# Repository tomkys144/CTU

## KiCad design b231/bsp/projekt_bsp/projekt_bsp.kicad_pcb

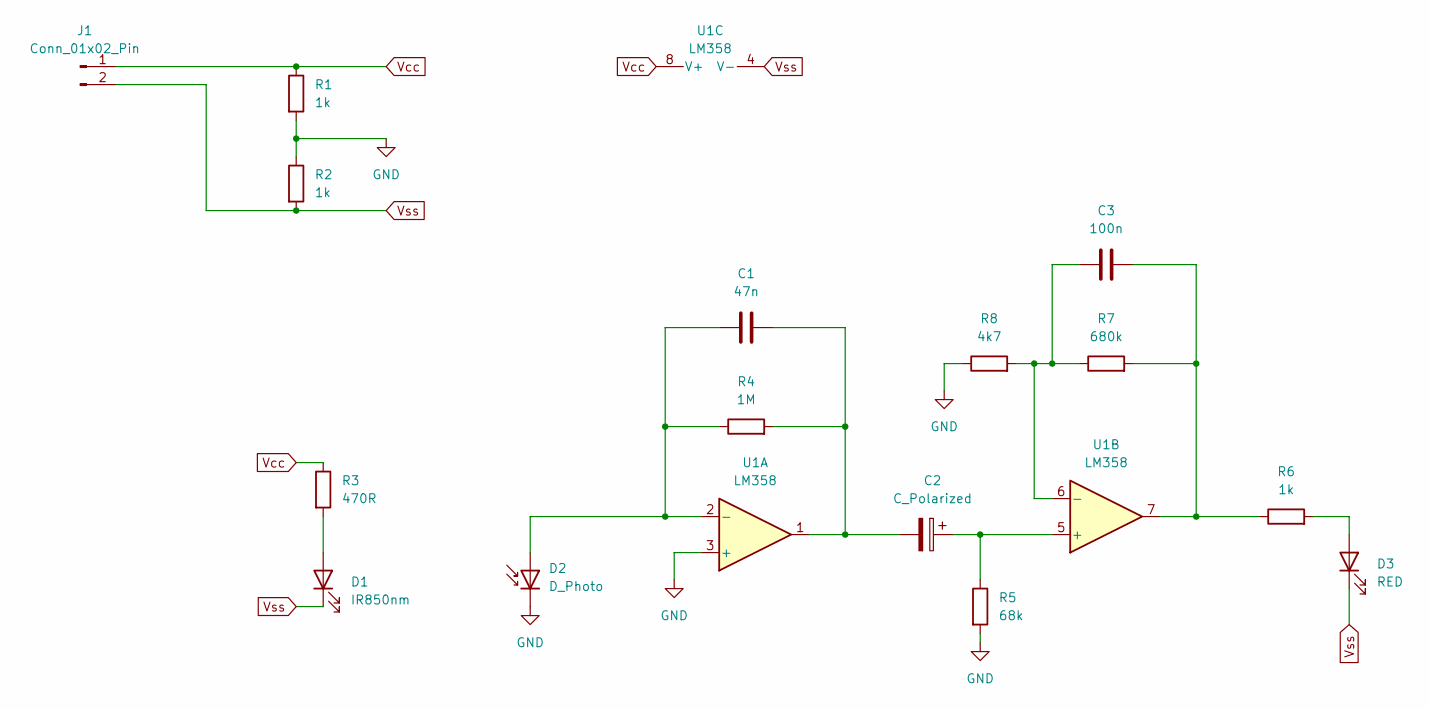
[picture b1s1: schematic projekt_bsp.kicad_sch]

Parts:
C1: 47n; C_Disc_D5.0mm_W2.5mm_P2.50mm
C2: C_Polarized; C_Disc_D5.0mm_W2.5mm_P2.50mm
C3: 100n; C_Disc_D5.0mm_W2.5mm_P2.50mm
D1: IR850nm; LED_D5.0mm
D2: D_Photo; LED_D5.0mm
D3: RED; LED_D5.0mm
J1: Conn_01x02_Pin; PinHeader_1x02_P2.54mm_Vertical
R1, R2, R6: 1k; R_Axial_DIN0207_L6.3mm_D2.5mm_P10.16mm_Horizontal
R3: 470R; R_Axial_DIN0207_L6.3mm_D2.5mm_P10.16mm_Horizontal
R4: 1M; R_Axial_DIN0207_L6.3mm_D2.5mm_P10.16mm_Horizontal
R5: 68k; R_Axial_DIN0207_L6.3mm_D2.5mm_P10.16mm_Horizontal
R7: 680k; R_Axial_DIN0207_L6.3mm_D2.5mm_P10.16mm_Horizontal
R8: 4k7; R_Axial_DIN0207_L6.3mm_D2.5mm_P10.16mm_Horizontal
U1: LM358; DIP-8_W7.62mm_Socket_LongPads

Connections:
GND: D2.1 (K), R1.2, R2.1, R5.2, R8.1, U1.3 (+)
unnamed: C1.2, C2.2, R4.2, U1.1
unnamed: C3.2, R6.1, R7.2, U1.7
unnamed: D1.2 (A), R3.2
unnamed: C1.1, D2.2 (A), R4.1, U1.2 (-)
unnamed: D3.2 (A), R6.2
unnamed: C2.1, R5.1, U1.5 (+)
unnamed: C3.1, R7.1, R8.2, U1.6 (-)
Vcc: J1.1, R1.1, R3.1, U1.8 (V+)
Vss: D1.1 (K), D3.1 (K), J1.2, R2.2, U1.4 (V-)

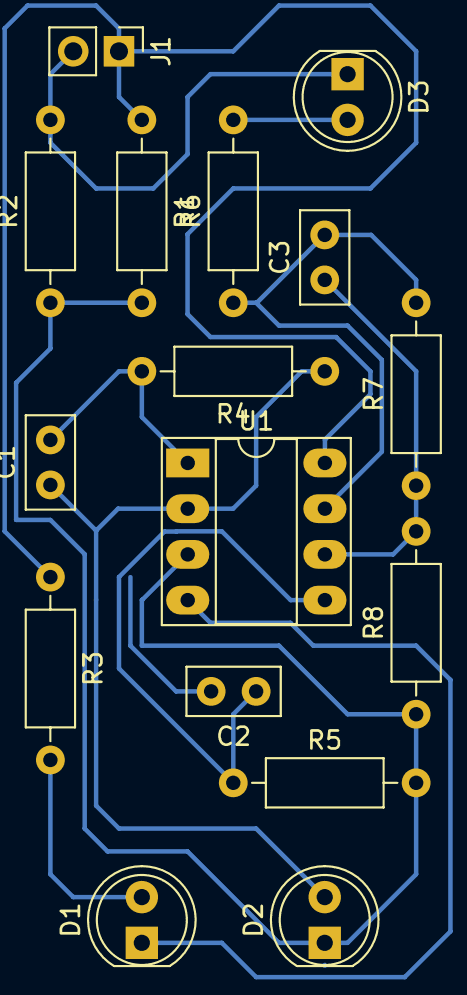
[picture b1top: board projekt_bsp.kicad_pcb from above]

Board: 2 copper layers, 16 parts (0 on the bottom side), 10 nets.

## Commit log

2020-11-14 Added ZPR
2020-11-14 Synced all materials for AF1, LAGA, MA1
2020-11-14 Added info about semestr
2020-11-16 Fixed typo
2020-11-18 Added Osovy skelet in b201/AF1
2020-11-18 added ZPR submodule
2020-11-18 updated .gitmodules
2020-11-22 Added ukol4 in b201/MA1
2020-11-23 added 7th homework in b201/Biomechanics
2020-11-24 Updated Lebka in b201/AF1
2020-11-25 Added HW8 in b201/Biomechanics
2020-11-25 removed .idea
2020-11-27 updated zapis in b201/biomechanics
2020-12-03 added HW9 in b201/Biomechanics
2020-12-03 Update ZPR
2020-12-08 Added Test2 in 2201/LAGA & ukol5 in b201/MA
2020-12-09 Added muslec of upper limb in b201/anatomy
2020-12-09 Added HW10 in b201/biomechanics
2020-12-27 synced 27/12/2020
2021-02-18 Started new semestr
2021-02-18 repair
2021-02-18 started b202
2021-02-18 renamed muscles
2022-02-20 Sync
2022-02-20 sync b212
2022-02-20 Added LABs in EMA
2022-02-21 finished LAB1 in EMA
2022-02-21 Fixed typo in LAB1
2022-02-22 finished LAB3 in b212/EMA
2022-02-24 Pred01 in SAS
2022-02-26 Did homework for EMA LAB4
2022-02-27 finished LAB5 preparation
2022-03-13 added LAB2 in EMA
2022-03-21 Added LAB7 in EMA
2022-03-21 synced b202
2022-03-21 added LAB0 in FYZ
2022-04-03 finished LAB8
2022-04-11 Added LAB9
2022-04-18 started working on LAB03
2022-05-15 started working on LAB5
2024-09-18 Added whole bc study
2024-09-24 Started new semester
2024-10-02 2/10/2024
2024-10-04 4/10/2024
2024-10-06 Aaaaaaaa
2024-10-09 Uz dost, prosim
2024-10-13 Je to taaaam
2024-11-14 14/11/2024
2024-11-14 Added BioMEMS
2024-11-14 Added AEDA/lab8
2024-11-15 let project
2024-11-17 finished schematic
2024-11-23 LET project update
2024-12-23 PAL/HW6 works
2025-01-05 Added let project
2025-02-20 20/02/2025T11:06
2025-02-25 Added DSP and ZSL
2025-03-03 Added BSG/LAB02
2025-03-07 2025/03/07
    2025/03/07
2025-03-17 SMU HW1
2025-03-20 finished SMU/HW1
2025-03-25 Fixed submodules
2025-03-25 Added AOL project
2025-03-25 25/03/2025
2025-10-03 Started winter semester 2025
2025-10-03 Converting xopp to pdf
2025-10-03 Fixed MSP
2025-10-03 renambe graz to b251
2025-10-07 Started other classes
2025-10-11 Second week
2025-10-14 Start of third week
2025-10-16 16/10/2025
2025-10-28 Third exercise of NSP
2025-11-24 24/11/2025
2025-12-07 Finished my part of NSP/hw1
